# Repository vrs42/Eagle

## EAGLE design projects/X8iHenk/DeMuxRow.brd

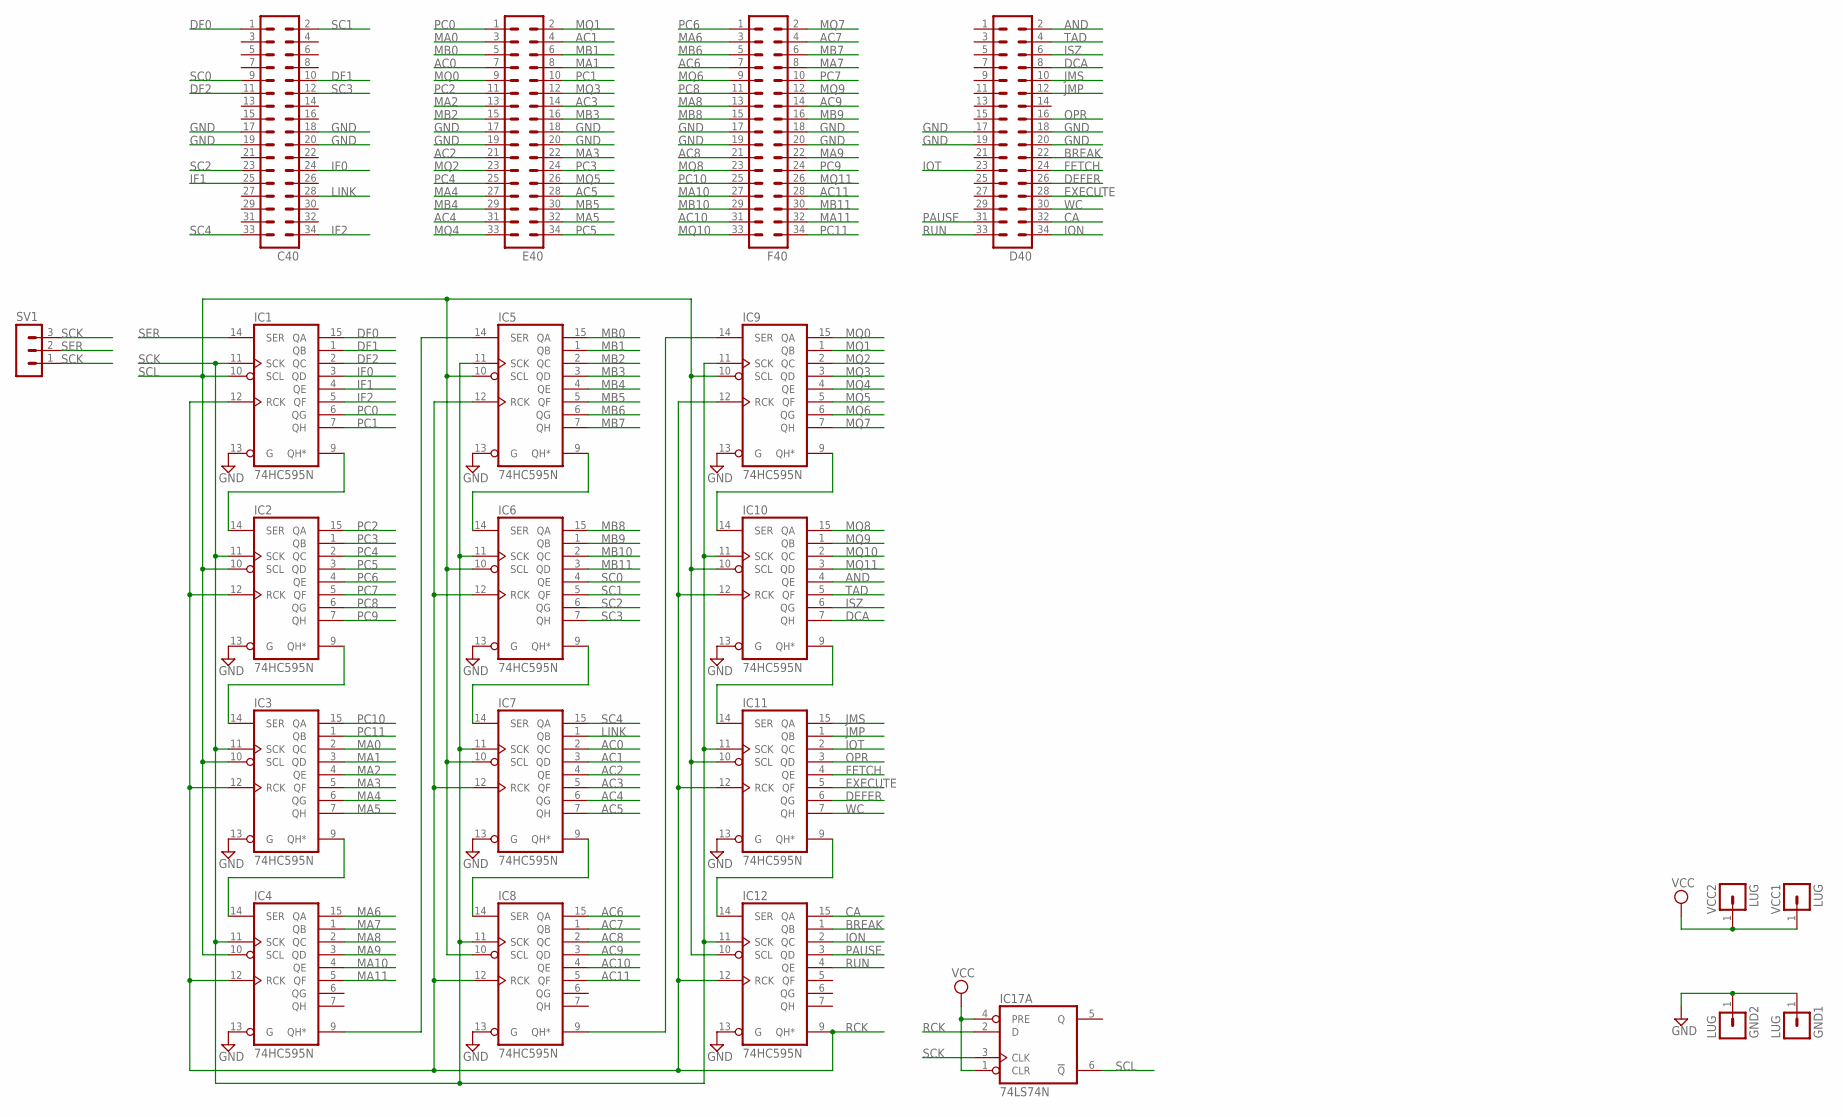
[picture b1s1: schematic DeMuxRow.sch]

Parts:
C40: MA17-2
D40: MA17-2
E40: MA17-2
F40: MA17-2
GND1, GND2: LUG; SPADELUG
IC1, IC2, IC3, IC4, IC5, IC6, IC7, IC8, IC9, IC10, IC11, IC12: 74HC595N; DIL16
IC17: 74LS74N; DIL14
SV1: MA03-1
VCC1, VCC2: LUG; SPADELUG

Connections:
AC0: E40.7, IC7.2 (QC)
AC1: E40.4, IC7.3 (QD)
AC2: E40.21, IC7.4 (QE)
AC3: E40.14, IC7.5 (QF)
AC4: E40.31, IC7.6 (QG)
AC5: E40.28, IC7.7 (QH)
AC6: F40.7, IC8.15 (QA)
AC7: F40.4, IC8.1 (QB)
AC8: F40.21, IC8.2 (QC)
AC9: F40.14, IC8.3 (QD)
AC10: F40.31, IC8.4 (QE)
AC11: F40.28, IC8.5 (QF)
AND: D40.2, IC10.4 (QE)
BREAK: D40.22, IC12.1 (QB)
CA: D40.32, IC12.15 (QA)
DCA: D40.8, IC10.7 (QH)
DEFER: D40.26, IC11.6 (QG)
DF0: C40.1, IC1.15 (QA)
DF1: C40.10, IC1.1 (QB)
DF2: C40.11, IC1.2 (QC)
EXECUTE: D40.28, IC11.5 (QF)
FETCH: D40.24, IC11.4 (QE)
GND: C40.17, C40.18, C40.19, C40.20, D40.17, D40.18, D40.19, D40.20, E40.17, E40.18, E40.19, E40.20, F40.17, F40.18, F40.19, F40.20, GND1.1, GND2.1, IC1.8 (GND), IC1.13 (G), IC2.8 (GND), IC2.13 (G), IC3.8 (GND), IC3.13 (G), IC4.8 (GND), IC4.13 (G), IC5.8 (GND), IC5.13 (G), IC6.8 (GND), IC6.13 (G), IC7.8 (GND), IC7.13 (G), IC8.8 (GND), IC8.13 (G), IC9.8 (GND), IC9.13 (G), IC10.8 (GND), IC10.13 (G), IC11.8 (GND), IC11.13 (G), IC12.8 (GND), IC12.13 (G), IC17.7 (GND)
IF0: C40.24, IC1.3 (QD)
IF1: C40.25, IC1.4 (QE)
IF2: C40.34, IC1.5 (QF)
ION: D40.34, IC12.2 (QC)
IOT: D40.23, IC11.2 (QC)
ISZ: D40.6, IC10.6 (QG)
JMP: D40.12, IC11.1 (QB)
JMS: D40.10, IC11.15 (QA)
LINK: C40.28, IC7.1 (QB)
MA0: E40.3, IC3.2 (QC)
MA1: E40.8, IC3.3 (QD)
MA2: E40.13, IC3.4 (QE)
MA3: E40.22, IC3.5 (QF)
MA4: E40.27, IC3.6 (QG)
MA5: E40.32, IC3.7 (QH)
MA6: F40.3, IC4.15 (QA)
MA7: F40.8, IC4.1 (QB)
MA8: F40.13, IC4.2 (QC)
MA9: F40.22, IC4.3 (QD)
MA10: F40.27, IC4.4 (QE)
MA11: F40.32, IC4.5 (QF)
MB0: E40.5, IC5.15 (QA)
MB1: E40.6, IC5.1 (QB)
MB2: E40.15, IC5.2 (QC)
MB3: E40.16, IC5.3 (QD)
MB4: E40.29, IC5.4 (QE)
MB5: E40.30, IC5.5 (QF)
MB6: F40.5, IC5.6 (QG)
MB7: F40.6, IC5.7 (QH)
MB8: F40.15, IC6.15 (QA)
MB9: F40.16, IC6.1 (QB)
MB10: F40.29, IC6.2 (QC)
MB11: F40.30, IC6.3 (QD)
MQ0: E40.9, IC9.15 (QA)
MQ1: E40.2, IC9.1 (QB)
MQ2: E40.23, IC9.2 (QC)
MQ3: E40.12, IC9.3 (QD)
MQ4: E40.33, IC9.4 (QE)
MQ5: E40.26, IC9.5 (QF)
MQ6: F40.9, IC9.6 (QG)
MQ7: F40.2, IC9.7 (QH)
MQ8: F40.23, IC10.15 (QA)
MQ9: F40.12, IC10.1 (QB)
MQ10: F40.33, IC10.2 (QC)
MQ11: F40.26, IC10.3 (QD)
unnamed: IC5.9 (QH*), IC6.14 (SER)
unnamed: IC1.9 (QH*), IC2.14 (SER)
unnamed: IC2.9 (QH*), IC3.14 (SER)
unnamed: IC3.9 (QH*), IC4.14 (SER)
unnamed: IC7.9 (QH*), IC8.14 (SER)
unnamed: IC6.9 (QH*), IC7.14 (SER)
unnamed: IC11.9 (QH*), IC12.14 (SER)
unnamed: IC10.9 (QH*), IC11.14 (SER)
unnamed: IC9.9 (QH*), IC10.14 (SER)
unnamed: IC4.9 (QH*), IC5.14 (SER)
unnamed: IC8.9 (QH*), IC9.14 (SER)
OPR: D40.16, IC11.3 (QD)
PAUSE: D40.31, IC12.3 (QD)
PC0: E40.1, IC1.6 (QG)
PC1: E40.10, IC1.7 (QH)
PC2: E40.11, IC2.15 (QA)
PC3: E40.24, IC2.1 (QB)
PC4: E40.25, IC2.2 (QC)
PC5: E40.34, IC2.3 (QD)
PC6: F40.1, IC2.4 (QE)
PC7: F40.10, IC2.5 (QF)
PC8: F40.11, IC2.6 (QG)
PC9: F40.24, IC2.7 (QH)
PC10: F40.25, IC3.15 (QA)
PC11: F40.34, IC3.1 (QB)
RCK: IC1.12 (RCK), IC2.12 (RCK), IC3.12 (RCK), IC4.12 (RCK), IC5.12 (RCK), IC6.12 (RCK), IC7.12 (RCK), IC8.12 (RCK), IC9.12 (RCK), IC10.12 (RCK), IC11.12 (RCK), IC12.9 (QH*), IC12.12 (RCK), IC17.2 (D)
RUN: D40.33, IC12.4 (QE)
SC0: C40.9, IC6.4 (QE)
SC1: C40.2, IC6.5 (QF)
SC2: C40.23, IC6.6 (QG)
SC3: C40.12, IC6.7 (QH)
SC4: C40.33, IC7.15 (QA)
SCK: IC1.11 (SCK), IC2.11 (SCK), IC3.11 (SCK), IC4.11 (SCK), IC5.11 (SCK), IC6.11 (SCK), IC7.11 (SCK), IC8.11 (SCK), IC9.11 (SCK), IC10.11 (SCK), IC11.11 (SCK), IC12.11 (SCK), IC17.3 (CLK), SV1.1, SV1.3
SCL: IC1.10 (SCL), IC2.10 (SCL), IC3.10 (SCL), IC4.10 (SCL), IC5.10 (SCL), IC6.10 (SCL), IC7.10 (SCL), IC8.10 (SCL), IC9.10 (SCL), IC10.10 (SCL), IC11.10 (SCL), IC12.10 (SCL), IC17.6 (!Q)
SER: IC1.14 (SER), SV1.2
TAD: D40.4, IC10.5 (QF)
VCC: IC1.16 (VCC), IC2.16 (VCC), IC3.16 (VCC), IC4.16 (VCC), IC5.16 (VCC), IC6.16 (VCC), IC7.16 (VCC), IC8.16 (VCC), IC9.16 (VCC), IC10.16 (VCC), IC11.16 (VCC), IC12.16 (VCC), IC17.1 (CLR), IC17.4 (PRE), IC17.14 (VCC), VCC1.1, VCC2.1
WC: D40.30, IC11.7 (QH)

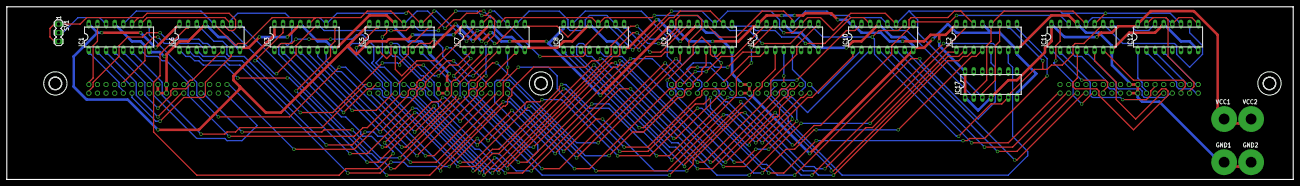
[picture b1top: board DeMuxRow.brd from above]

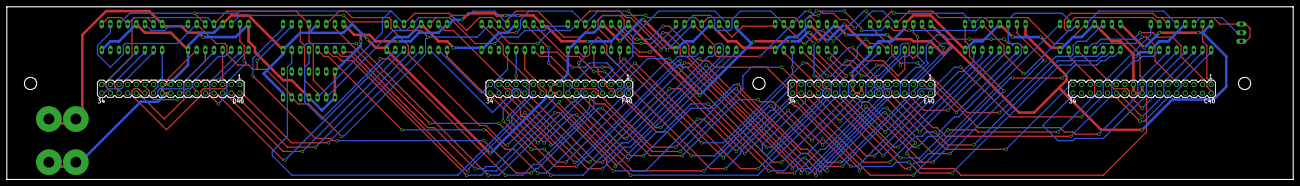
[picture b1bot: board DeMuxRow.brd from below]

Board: 2 copper layers, 378.5 x 50.8 mm, 25 parts (4 on the bottom side), 106 nets.

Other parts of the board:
U$5, U$9, U$11: 3,6

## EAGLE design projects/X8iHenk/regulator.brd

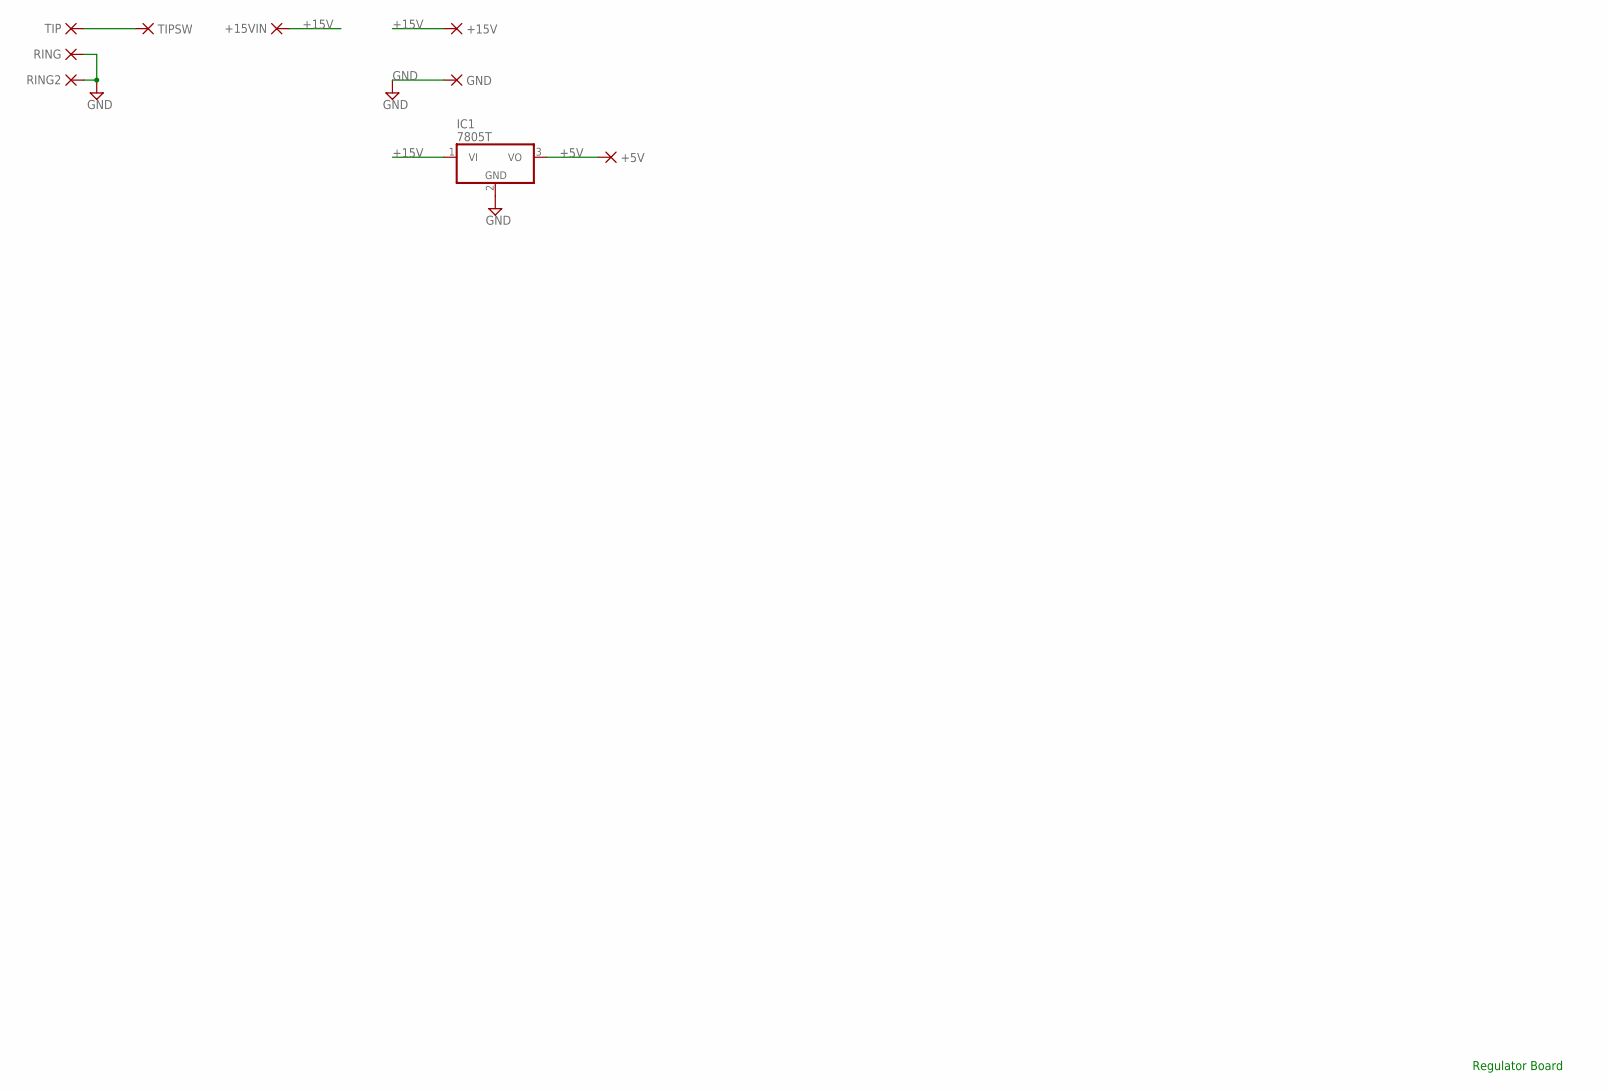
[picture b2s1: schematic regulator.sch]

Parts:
+5V, +15V, +15VIN: PAD-0635; 0635
GND: PAD-0635; 0635
IC1: 7805T; TO220H
RING, RING2: PAD-0635; 0635
TIP: PAD-0635; 0635
TIPSW: PAD-0635; 0635

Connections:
+5V: +5V.P$1, IC1.3 (VO)
+15V: +15V.P$1, +15VIN.P$1, IC1.1 (VI)
GND: GND.P$1, IC1.2 (GND), RING.P$1, RING2.P$1
unnamed: TIP.P$1, TIPSW.P$1

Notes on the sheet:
Regulator Board

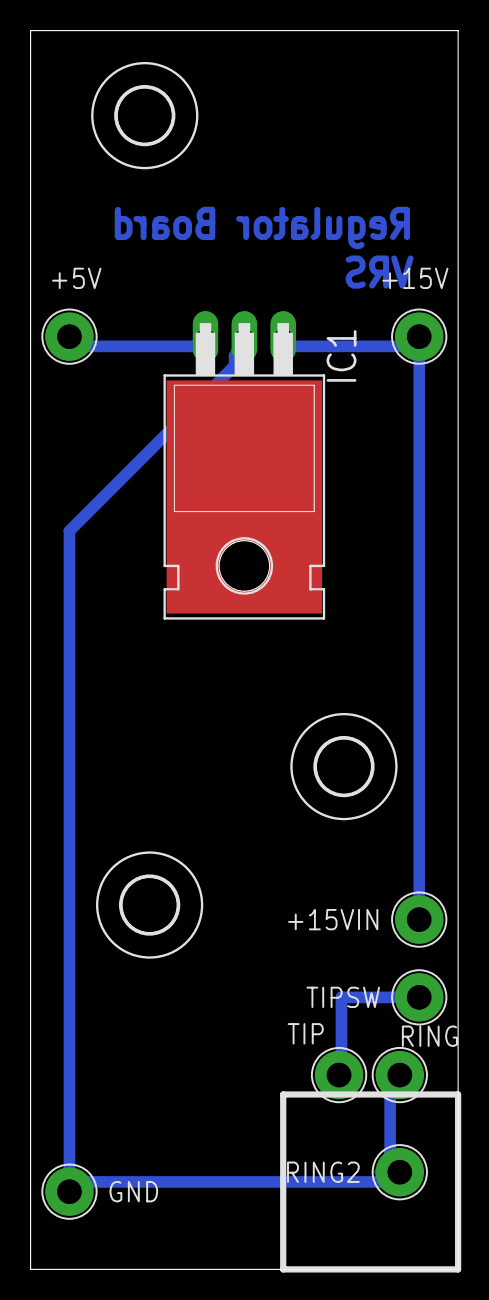
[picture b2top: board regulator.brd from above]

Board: 2 copper layers, 27.9 x 81.0 mm, 12 parts (0 on the bottom side), 4 nets.

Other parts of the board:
U$5, U$6, U$7: 3,6

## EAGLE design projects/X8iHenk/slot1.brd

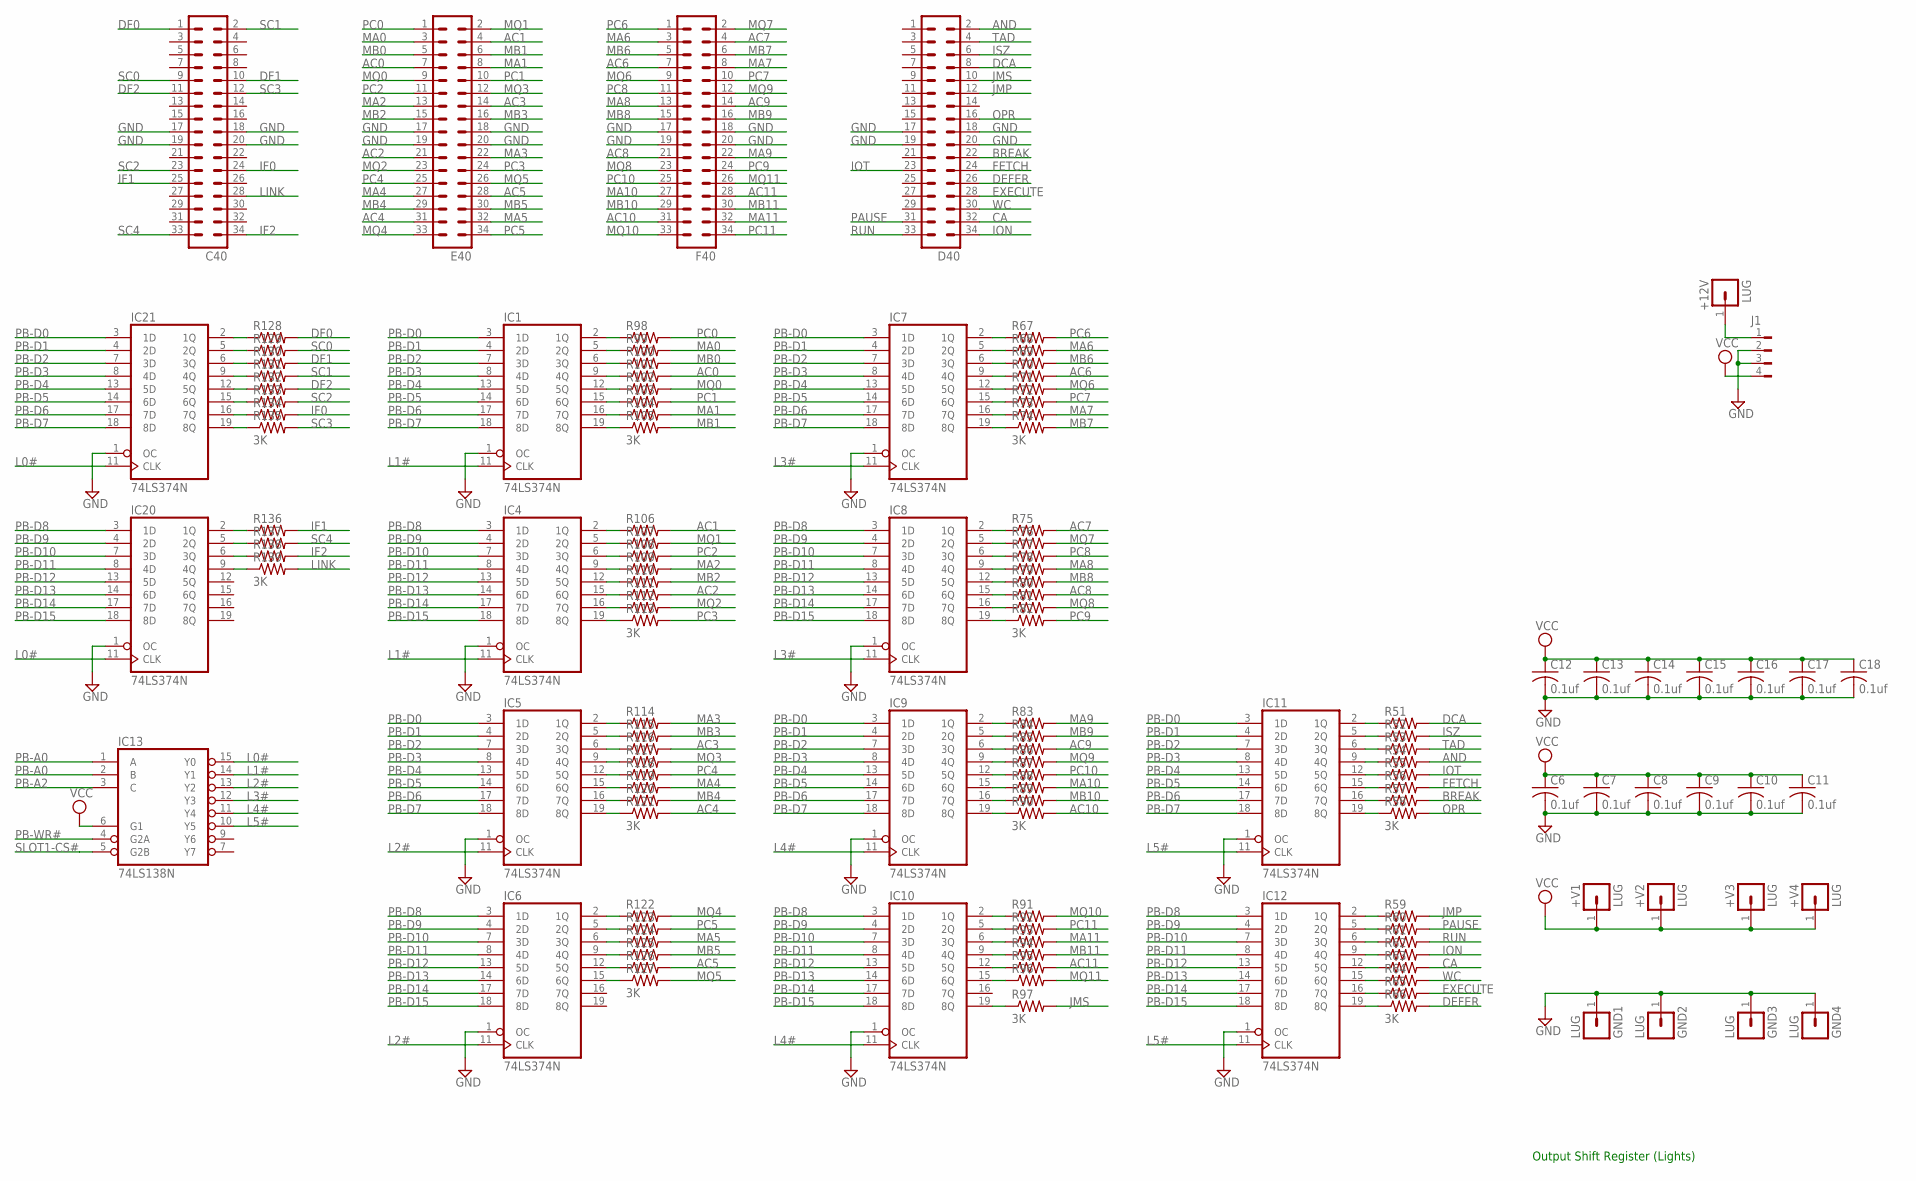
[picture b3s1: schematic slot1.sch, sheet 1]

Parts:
+12V: LUG; SPADELUG
+V1, +V2, +V3, +V4: LUG; SPADELUG
C6, C7, C8, C9, C10, C11, C12, C13, C14, C15, C16, C17, C18: 0.1uf; C050-025X075
C40: MA17-2
D40: MA17-2
E40: MA17-2
F40: MA17-2
GND1, GND2, GND3, GND4: LUG; SPADELUG
IC1, IC4, IC5, IC6, IC7, IC8, IC9, IC10, IC11, IC12, IC20, IC21: 74LS374N; DIL20
IC13: 74LS138N; DIL16
J1: FLOPPY-4
R51, R52, R53, R54, R55, R56, R57, R59, R60, R61, R62, R63, R64, R65, R67, R68, R69, R70, R71, R72, R73, R75, R76, R77, R78, R79, R80, R81, R83, R84, R85, R86, R87, R88, R89, R91, R92, R93, R94, R95, R96, R98, R99, R100, R101, R102, R103, R104, R106, R107, R108, R109, R110, R111, R112, R114, R115, R116, R117, R118, R119, R120, R122, R123, R124, R125, R126, R128, R129, R130, R131, R132, R133, R134, R136, R137, R138: R-US_0207/10; 0207/10
R58, R66, R74, R82, R90, R97, R105, R113, R121, R127, R135, R139: 3K; 0207/10

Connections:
+12V: +12V.1, J1.1
AC0: E40.7, R101.2
AC1: E40.4, R106.2
AC2: E40.21, R111.2
AC3: E40.14, R116.2
AC4: E40.31, R121.2
AC5: E40.28, R126.2
AC6: F40.7, R70.2
AC7: F40.4, R75.2
AC8: F40.21, R80.2
AC9: F40.14, R85.2
AC10: F40.31, R90.2
AC11: F40.28, R95.2
AND: D40.2, R54.2
BREAK: D40.22, R57.2
CA: D40.32, R63.2
DCA: D40.8, R51.2
DEFER: D40.26, R66.2
DF0: C40.1, R128.2
DF1: C40.10, R130.2
DF2: C40.11, R132.2
EXECUTE: D40.28, R65.2
FETCH: D40.24, R56.2
GND: C6.2, C7.2, C8.2, C9.2, C10.2, C11.2, C12.2, C13.2, C14.2, C15.2, C16.2, C17.2, C18.2, C40.17, C40.18, C40.19, C40.20, D40.17, D40.18, D40.19, D40.20, E40.17, E40.18, E40.19, E40.20, F40.17, F40.18, F40.19, F40.20, GND1.1, GND2.1, GND3.1, GND4.1, IC1.1 (OC), IC1.10 (GND), IC4.1 (OC), IC4.10 (GND), IC5.1 (OC), IC5.10 (GND), IC6.1 (OC), IC6.10 (GND), IC7.1 (OC), IC7.10 (GND), IC8.1 (OC), IC8.10 (GND), IC9.1 (OC), IC9.10 (GND), IC10.1 (OC), IC10.10 (GND), IC11.1 (OC), IC11.10 (GND), IC12.1 (OC), IC12.10 (GND), IC13.8 (GND), IC20.1 (OC), IC20.10 (GND), IC21.1 (OC), IC21.10 (GND), J1.2, J1.3; also elsewhere on the board
IF0: C40.24, R134.2
IF1: C40.25, R136.2
IF2: C40.34, R138.2
ION: D40.34, R62.2
IOT: D40.23, R55.2
ISZ: D40.6, R52.2
JMP: D40.12, R59.2
JMS: D40.10, R97.2
L0#: IC13.15 (Y0), IC20.11 (CLK), IC21.11 (CLK)
L1#: IC1.11 (CLK), IC4.11 (CLK), IC13.14 (Y1)
L2#: IC5.11 (CLK), IC6.11 (CLK), IC13.13 (Y2)
L3#: IC7.11 (CLK), IC8.11 (CLK), IC13.12 (Y3)
L4#: IC9.11 (CLK), IC10.11 (CLK), IC13.11 (Y4)
L5#: IC11.11 (CLK), IC12.11 (CLK), IC13.10 (Y5)
LINK: C40.28, R139.2
MA0: E40.3, R99.2
MA1: E40.8, R104.2
MA2: E40.13, R109.2
MA3: E40.22, R114.2
MA4: E40.27, R119.2
MA5: E40.32, R124.2
MA6: F40.3, R68.2
MA7: F40.8, R73.2
MA8: F40.13, R78.2
MA9: F40.22, R83.2
MA10: F40.27, R88.2
MA11: F40.32, R93.2
MB0: E40.5, R100.2
MB1: E40.6, R105.2
MB2: E40.15, R110.2
MB3: E40.16, R115.2
MB4: E40.29, R120.2
MB5: E40.30, R125.2
MB6: F40.5, R69.2
MB7: F40.6, R74.2
MB8: F40.15, R79.2
MB9: F40.16, R84.2
MB10: F40.29, R89.2
MB11: F40.30, R94.2
MQ0: E40.9, R102.2
MQ1: E40.2, R107.2
MQ2: E40.23, R112.2
MQ3: E40.12, R117.2
MQ4: E40.33, R122.2
MQ5: E40.26, R127.2
MQ6: F40.9, R71.2
MQ7: F40.2, R76.2
MQ8: F40.23, R81.2
MQ9: F40.12, R86.2
MQ10: F40.33, R91.2
MQ11: F40.26, R96.2
unnamed: IC11.2 (1Q), R51.1
unnamed: IC11.5 (2Q), R52.1
unnamed: IC11.6 (3Q), R53.1
unnamed: IC11.9 (4Q), R54.1
unnamed: IC11.12 (5Q), R55.1
unnamed: IC11.15 (6Q), R56.1
unnamed: IC11.16 (7Q), R57.1
unnamed: IC11.19 (8Q), R58.1
unnamed: IC12.2 (1Q), R59.1
unnamed: IC12.5 (2Q), R60.1
unnamed: IC12.6 (3Q), R61.1
unnamed: IC12.9 (4Q), R62.1
unnamed: IC12.12 (5Q), R63.1
unnamed: IC12.15 (6Q), R64.1
unnamed: IC12.16 (7Q), R65.1
unnamed: IC12.19 (8Q), R66.1
unnamed: IC7.2 (1Q), R67.1
unnamed: IC7.5 (2Q), R68.1
unnamed: IC7.6 (3Q), R69.1
unnamed: IC7.9 (4Q), R70.1
unnamed: IC7.12 (5Q), R71.1
unnamed: IC7.15 (6Q), R72.1
unnamed: IC7.16 (7Q), R73.1
unnamed: IC7.19 (8Q), R74.1
unnamed: IC10.19 (8Q), R97.1
unnamed: IC10.15 (6Q), R96.1
unnamed: IC10.12 (5Q), R95.1
unnamed: IC10.9 (4Q), R94.1
unnamed: IC10.6 (3Q), R93.1
unnamed: IC10.5 (2Q), R92.1
unnamed: IC10.2 (1Q), R91.1
unnamed: IC8.2 (1Q), R75.1
unnamed: IC8.5 (2Q), R76.1
unnamed: IC8.6 (3Q), R77.1
unnamed: IC8.9 (4Q), R78.1
unnamed: IC8.12 (5Q), R79.1
unnamed: IC8.15 (6Q), R80.1
unnamed: IC8.16 (7Q), R81.1
unnamed: IC8.19 (8Q), R82.1
unnamed: IC9.2 (1Q), R83.1
unnamed: IC9.5 (2Q), R84.1
unnamed: IC9.9 (4Q), R86.1
unnamed: IC9.6 (3Q), R85.1
unnamed: IC9.12 (5Q), R87.1
unnamed: IC9.15 (6Q), R88.1
unnamed: IC9.16 (7Q), R89.1
unnamed: IC9.19 (8Q), R90.1
unnamed: IC6.15 (6Q), R127.1
unnamed: IC6.12 (5Q), R126.1
unnamed: IC6.9 (4Q), R125.1
unnamed: IC6.6 (3Q), R124.1
unnamed: IC6.5 (2Q), R123.1
unnamed: IC6.2 (1Q), R122.1
unnamed: IC5.19 (8Q), R121.1
unnamed: IC5.16 (7Q), R120.1
unnamed: IC5.15 (6Q), R119.1
unnamed: IC5.12 (5Q), R118.1
unnamed: IC5.9 (4Q), R117.1
unnamed: IC5.6 (3Q), R116.1
unnamed: IC5.5 (2Q), R115.1
unnamed: IC5.2 (1Q), R114.1
unnamed: IC1.2 (1Q), R98.1
unnamed: IC1.5 (2Q), R99.1
unnamed: IC1.6 (3Q), R100.1
unnamed: IC1.9 (4Q), R101.1
unnamed: IC1.12 (5Q), R102.1
unnamed: IC1.15 (6Q), R103.1
unnamed: IC1.16 (7Q), R104.1
unnamed: IC1.19 (8Q), R105.1
unnamed: IC4.2 (1Q), R106.1
unnamed: IC4.5 (2Q), R107.1
unnamed: IC4.6 (3Q), R108.1
unnamed: IC4.9 (4Q), R109.1
unnamed: IC4.12 (5Q), R110.1
unnamed: IC4.15 (6Q), R111.1
unnamed: IC4.16 (7Q), R112.1
unnamed: IC4.19 (8Q), R113.1
unnamed: IC21.2 (1Q), R128.1
unnamed: IC21.5 (2Q), R129.1
unnamed: IC21.6 (3Q), R130.1
unnamed: IC21.9 (4Q), R131.1
unnamed: IC21.12 (5Q), R132.1
unnamed: IC21.15 (6Q), R133.1
unnamed: IC21.16 (7Q), R134.1
unnamed: IC21.19 (8Q), R135.1
unnamed: IC20.2 (1Q), R136.1
unnamed: IC20.9 (4Q), R139.1
unnamed: IC20.6 (3Q), R138.1
unnamed: IC20.5 (2Q), R137.1
OPR: D40.16, R58.2
PAUSE: D40.31, R60.2
PB-A0: IC13.1 (A), IC13.2 (B); also elsewhere on the board
PB-A2: IC13.3 (C); also elsewhere on the board
PB-D0: IC1.3 (1D), IC5.3 (1D), IC7.3 (1D), IC9.3 (1D), IC11.3 (1D), IC21.3 (1D); also elsewhere on the board
PB-D1: IC1.4 (2D), IC5.4 (2D), IC7.4 (2D), IC9.4 (2D), IC11.4 (2D), IC21.4 (2D); also elsewhere on the board
PB-D2: IC1.7 (3D), IC5.7 (3D), IC7.7 (3D), IC9.7 (3D), IC11.7 (3D), IC21.7 (3D); also elsewhere on the board
PB-D3: IC1.8 (4D), IC5.8 (4D), IC7.8 (4D), IC9.8 (4D), IC11.8 (4D), IC21.8 (4D); also elsewhere on the board
PB-D4: IC1.13 (5D), IC5.13 (5D), IC7.13 (5D), IC9.13 (5D), IC11.13 (5D), IC21.13 (5D); also elsewhere on the board
PB-D5: IC1.14 (6D), IC5.14 (6D), IC7.14 (6D), IC9.14 (6D), IC11.14 (6D), IC21.14 (6D); also elsewhere on the board
PB-D6: IC1.17 (7D), IC5.17 (7D), IC7.17 (7D), IC9.17 (7D), IC11.17 (7D), IC21.17 (7D); also elsewhere on the board
PB-D7: IC1.18 (8D), IC5.18 (8D), IC7.18 (8D), IC9.18 (8D), IC11.18 (8D), IC21.18 (8D); also elsewhere on the board
PB-D8: IC4.3 (1D), IC6.3 (1D), IC8.3 (1D), IC10.3 (1D), IC12.3 (1D), IC20.3 (1D); also elsewhere on the board
PB-D9: IC4.4 (2D), IC6.4 (2D), IC8.4 (2D), IC10.4 (2D), IC12.4 (2D), IC20.4 (2D); also elsewhere on the board
PB-D10: IC4.7 (3D), IC6.7 (3D), IC8.7 (3D), IC10.7 (3D), IC12.7 (3D), IC20.7 (3D); also elsewhere on the board
PB-D11: IC4.8 (4D), IC6.8 (4D), IC8.8 (4D), IC10.8 (4D), IC12.8 (4D), IC20.8 (4D); also elsewhere on the board
PB-D12: IC4.13 (5D), IC6.13 (5D), IC8.13 (5D), IC10.13 (5D), IC12.13 (5D), IC20.13 (5D); also elsewhere on the board
PB-D13: IC4.14 (6D), IC6.14 (6D), IC8.14 (6D), IC10.14 (6D), IC12.14 (6D), IC20.14 (6D); also elsewhere on the board
PB-D14: IC4.17 (7D), IC6.17 (7D), IC8.17 (7D), IC10.17 (7D), IC12.17 (7D), IC20.17 (7D); also elsewhere on the board
PB-D15: IC4.18 (8D), IC6.18 (8D), IC8.18 (8D), IC10.18 (8D), IC12.18 (8D), IC20.18 (8D); also elsewhere on the board
PB-WR#: IC13.4 (G2A); also elsewhere on the board
PC0: E40.1, R98.2
PC1: E40.10, R103.2
PC2: E40.11, R108.2
PC3: E40.24, R113.2
PC4: E40.25, R118.2
PC5: E40.34, R123.2
PC6: F40.1, R67.2
PC7: F40.10, R72.2
PC8: F40.11, R77.2
PC9: F40.24, R82.2
PC10: F40.25, R87.2
PC11: F40.34, R92.2
RUN: D40.33, R61.2
SC0: C40.9, R129.2
SC1: C40.2, R131.2
SC2: C40.23, R133.2
SC3: C40.12, R135.2
SC4: C40.33, R137.2
SLOT1-CS#: IC13.5 (G2B); also elsewhere on the board
TAD: D40.4, R53.2
VCC: +V1.1, +V2.1, +V3.1, +V4.1, C6.1, C7.1, C8.1, C9.1, C10.1, C11.1, C12.1, C13.1, C14.1, C15.1, C16.1, C17.1, C18.1, IC1.20 (VCC), IC4.20 (VCC), IC5.20 (VCC), IC6.20 (VCC), IC7.20 (VCC), IC8.20 (VCC), IC9.20 (VCC), IC10.20 (VCC), IC11.20 (VCC), IC12.20 (VCC), IC13.6 (G1), IC13.16 (VCC), IC20.20 (VCC), IC21.20 (VCC), J1.4; also elsewhere on the board
WC: D40.30, R64.2

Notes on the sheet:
Output Shift Register (Lights)

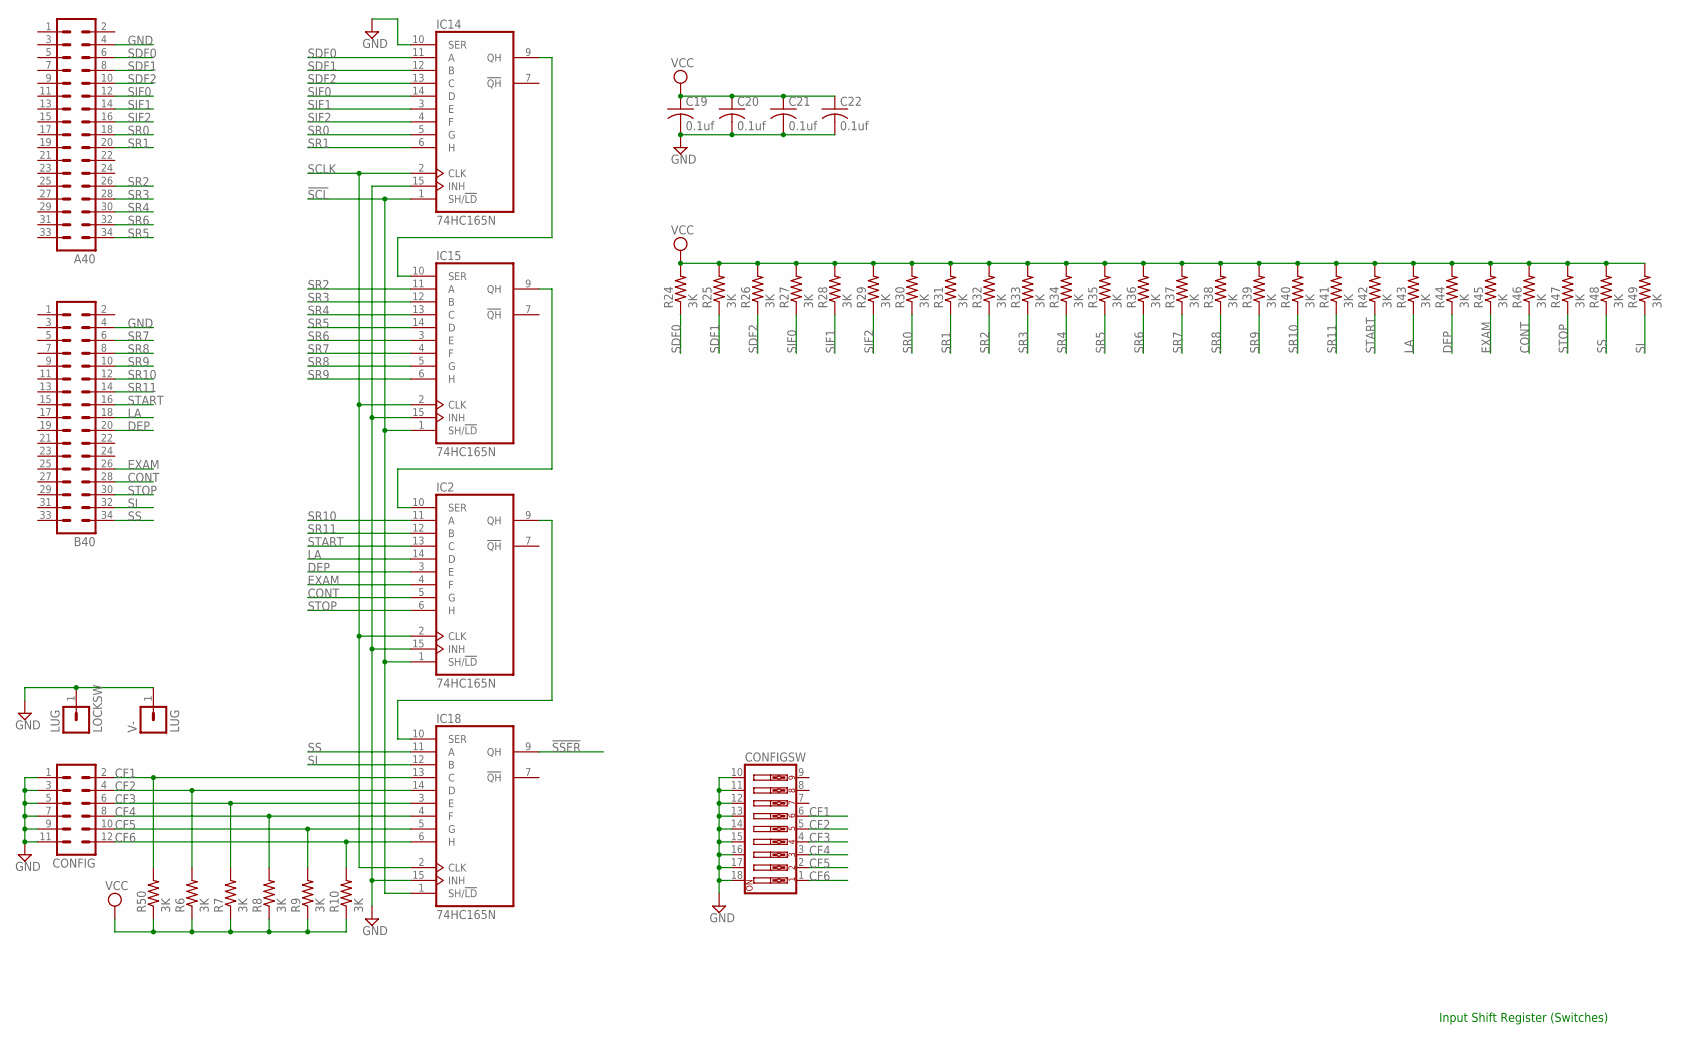
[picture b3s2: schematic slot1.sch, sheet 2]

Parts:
A40: MA17-2
B40: MA17-2
C19, C20, C21, C22: 0.1uf; C050-025X075
CONFIG: MA06-2
CONFIGSW: SW_DIP-9; EDG-09
IC2, IC14, IC15, IC18: 74HC165N; DIL16
LOCKSW: LUG; SPADELUG
R6, R7, R8, R9, R10, R24, R25, R26, R27, R28, R29, R30, R31, R32, R33, R34, R35, R36, R37, R38, R39, R40, R41, R42, R43, R44, R45, R46, R47, R48, R49, R50: 3K; 0207/10
V-: LUG; SPADELUG

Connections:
!SCL: IC2.1 (SH/!LD), IC14.1 (SH/!LD), IC15.1 (SH/!LD), IC18.1 (SH/!LD); also elsewhere on the board
!SSER: IC18.9 (QH); also elsewhere on the board
CF1: CONFIG.2, CONFIGSW.6, IC18.13 (C), R50.2
CF2: CONFIG.4, CONFIGSW.5, IC18.14 (D), R6.2
CF3: CONFIG.6, CONFIGSW.4, IC18.3 (E), R7.2
CF4: CONFIG.8, CONFIGSW.3, IC18.4 (F), R8.2
CF5: CONFIG.10, CONFIGSW.2, IC18.5 (G), R9.2
CF6: CONFIG.12, CONFIGSW.1, IC18.6 (H), R10.2
CONT: B40.28, IC2.5 (G), R46.1
DEP: B40.20, IC2.3 (E), R44.1
EXAM: B40.26, IC2.4 (F), R45.1
GND: A40.4, B40.4, C19.2, C20.2, C21.2, C22.2, CONFIG.1, CONFIG.3, CONFIG.5, CONFIG.7, CONFIG.9, CONFIG.11, CONFIGSW.10, CONFIGSW.11, CONFIGSW.12, CONFIGSW.13, CONFIGSW.14, CONFIGSW.15, CONFIGSW.16, CONFIGSW.17, CONFIGSW.18, IC2.8 (GND), IC2.15 (INH), IC14.8 (GND), IC14.10 (SER), IC14.15 (INH), IC15.8 (GND), IC15.15 (INH), IC18.8 (GND), IC18.15 (INH), LOCKSW.1, V-.1; also elsewhere on the board
LA: B40.18, IC2.14 (D), R43.1
unnamed: IC14.9 (QH), IC15.10 (SER)
unnamed: IC2.10 (SER), IC15.9 (QH)
unnamed: IC2.9 (QH), IC18.10 (SER)
SCLK: IC2.2 (CLK), IC14.2 (CLK), IC15.2 (CLK), IC18.2 (CLK); also elsewhere on the board
SDF0: A40.6, IC14.11 (A), R24.1
SDF1: A40.8, IC14.12 (B), R25.1
SDF2: A40.10, IC14.13 (C), R26.1
SI: B40.32, IC18.12 (B), R49.1
SIF0: A40.12, IC14.14 (D), R27.1
SIF1: A40.14, IC14.3 (E), R28.1
SIF2: A40.16, IC14.4 (F), R29.1
SR0: A40.18, IC14.5 (G), R30.1
SR1: A40.20, IC14.6 (H), R31.1
SR2: A40.26, IC15.11 (A), R32.1
SR3: A40.28, IC15.12 (B), R33.1
SR4: A40.30, IC15.13 (C), R34.1
SR5: A40.34, IC15.14 (D), R35.1
SR6: A40.32, IC15.3 (E), R36.1
SR7: B40.6, IC15.4 (F), R37.1
SR8: B40.8, IC15.5 (G), R38.1
SR9: B40.10, IC15.6 (H), R39.1
SR10: B40.12, IC2.11 (A), R40.1
SR11: B40.14, IC2.12 (B), R41.1
SS: B40.34, IC18.11 (A), R48.1
START: B40.16, IC2.13 (C), R42.1
STOP: B40.30, IC2.6 (H), R47.1
VCC: C19.1, C20.1, C21.1, C22.1, IC2.16 (VCC), IC14.16 (VCC), IC15.16 (VCC), IC18.16 (VCC), R6.1, R7.1, R8.1, R9.1, R10.1, R24.2, R25.2, R26.2, R27.2, R28.2, R29.2, R30.2, R31.2, R32.2, R33.2, R34.2, R35.2, R36.2, R37.2, R38.2, R39.2, R40.2, R41.2, R42.2, R43.2, R44.2, R45.2, R46.2, R47.2, R48.2, R49.2, R50.1; also elsewhere on the board

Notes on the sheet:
Input Shift Register (Switches)
